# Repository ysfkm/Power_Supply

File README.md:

# Power Supply

## Summary
- Custom linear-regulator power supply boards providing multiple regulated rails from a raw input voltage.
- **v0.1:** 24V input board with four fixed regulators (15V, 12V, 5V, 3V3) plus two variable outputs via jumpers and a buck converter; four-layer 157.5mm x 100mm PCB.
- **v1.1:** Revised ±15V input board delivering +12V and -5V, entirely from linear regulators (12V now derived from 15V instead of 24V, plus a new -5V rail); same 4-layer 157.5mm x 100mm PCB footprint.

## v0.1

### Specs
- **Input:** +24V
- **Output:** +15V, +12V, +5V, +3V3, two variable voltage outputs
- **Description:** one output for each voltage value and two variable outputs via jumpers. Uses four regulators and one buck converter.
- **PCB:** 157.5mm x 100mm / 4 Layer

### 15V Voltage Regulator
- **Input:** 24V, GNDA
- **Output:** 15V, GNDA
- **Maximum Output Current:** 1A
- **Thermal Resistance:** 44.8°C/W

### 12V Voltage Regulator
- **Input:** 24V, GNDA
- **Output:** 12V, GNDA
- **Maximum Output Current:** 1A
- **Thermal Resistance:** 44.8°C/W

### 5V Voltage Regulator
- **Input:** 24V, GNDA
- **Output:** 5V, GNDA
- **Maximum Output Current:** 1.2A
- **9V Buck Converter Thermal Resistance:** 50°C/W
- **5V Linear Regulator Thermal Resistance:** 44.8°C/W

### 3V3 Voltage Regulator
- **Input:** 9V, GNDA
- **Output:** 3V3, GNDA
- **Maximum Output Current:** 5A
- **Thermal Resistance:** 44.8°C/W

### Design Process
- Thermal vias for each regulator for heat dissipation
- Buck converter routed to minimize loop area of interference
- Built four voltage regulators separately, then tested out ideas on how to put together a combined power supply board
- Settled on two variable outputs and four constant outputs

## v1.1

### Specs
- **Input:** +15V, -15V, GNDA
- **Output:** +12V, -5V, GNDA
- **Description:** three output ports for each voltage value. All regulated from linear regulators
- **PCB:** 157.5mm x 100mm / 4 Layer

### 12V Voltage Regulator
- **Input:** 15V, GNDA
- **Output:** 12V, GNDA
- **Maximum Output Current:** 1.5A
- **Thermal Resistance:** 19°C/W

### -5V Voltage Regulator
- **Input:** -15V, GNDA
- **Output:** -5V, GNDA
- **Maximum Output Current:** 1A
- **Thermal Resistance:** 65°C/W

### Design Changes
- Needed -5V supply so made a new version of the board with 12V and -5V
- 12V now regulated from 15V instead of 24V, so used a different regulator

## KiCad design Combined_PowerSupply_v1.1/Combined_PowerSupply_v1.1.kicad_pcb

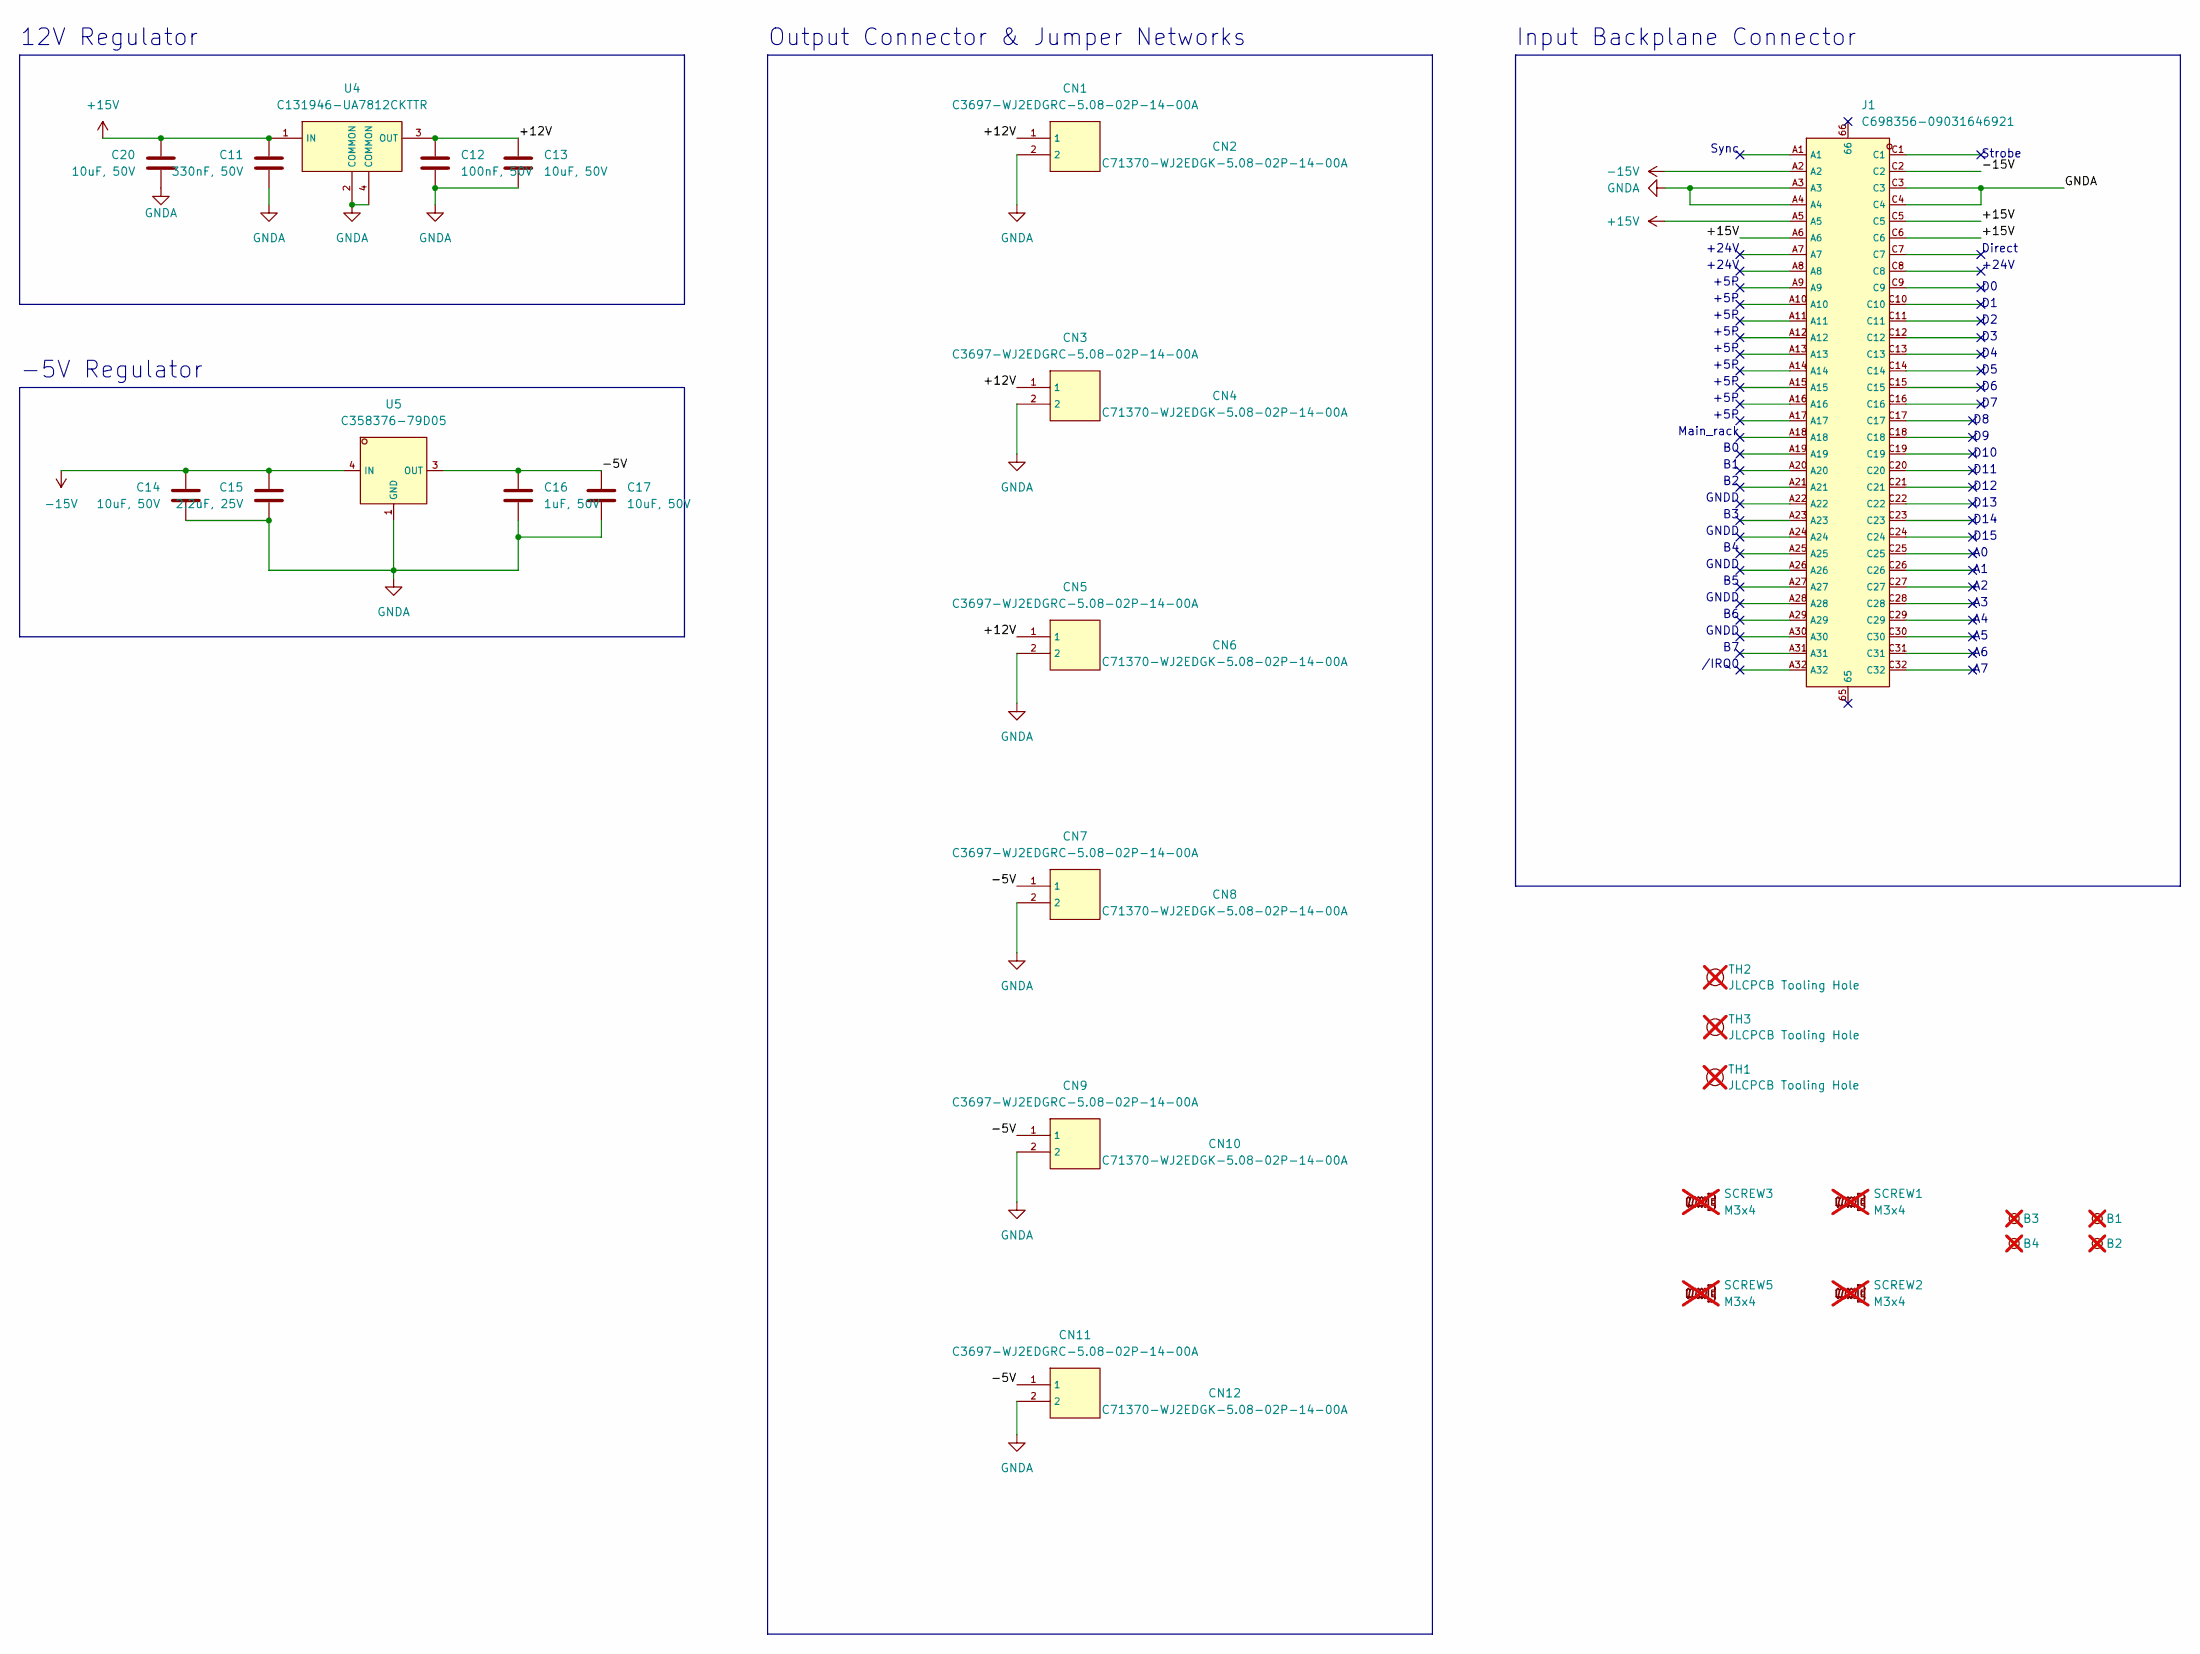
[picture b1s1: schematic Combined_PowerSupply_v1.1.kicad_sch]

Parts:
B1, B2, B3, B4: M3 Mounting Hole; MountingHole_3.2mm_M3_DIN965_Pad; not fitted
C11: 330nF, 50V; C_0603_1608Metric; LCSC C282682
C12: 100nF, 50V; C_0603_1608Metric; LCSC C14663
C13, C14, C17, C20: 10uF, 50V; C_1206_3216Metric; LCSC C13585
C15: 2.2uF, 25V; C_0603_1608Metric; LCSC C57895
C16: 1uF, 50V; C_0603_1608Metric; LCSC C15849
CN1, CN3, CN5, CN7, CN9, CN11: C3697-WJ2EDGRC-5.08-02P-14-00A; C3697-CONN-TH_2P-P5.08_WJ2EDGRC-5.08-2P; LCSC C3697
CN2, CN4, CN6, CN8, CN10, CN12: C71370-WJ2EDGK-5.08-02P-14-00A; C71370-FL_001; LCSC C71370
J1: C698356-09031646921; C698356-CONN-TH_64P-P2.54_HARTING_09031646921; LCSC C698356
SCREW1, SCREW2, SCREW3, SCREW5: M3x4; SCREW_M3; not fitted
TH1, TH2, TH3: JLCPCB Tooling Hole; ToolingHoles; not fitted
U4: C131946-UA7812CKTTR; C131946-TO-263-3L_L10.0-W9.2-P2.54-TL; LCSC C131946
U5: C358376-79D05; C358376-TO-252-2_L6.5-W6.1-P4.58-LS10.0-BR; LCSC C358376

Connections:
+15V: C11.1, C20.1, J1.A5, J1.A6, J1.C5, J1.C6, U4.1 (IN)
-15V: C14.1, C15.1, J1.A2, J1.C2, U5.4 (IN)
/+12V: C12.1, C13.1, CN1.1, CN3.1, CN5.1, U4.3 (OUT)
/-5V: C16.1, C17.1, CN7.1, CN9.1, CN11.1, U5.3 (OUT)
GNDA: C11.2, C12.2, C13.2, C14.2, C15.2, C16.2, C17.2, C20.2, CN1.2, CN3.2, CN5.2, CN7.2, CN9.2, CN11.2, J1.A3, J1.A4, J1.C3, J1.C4, U4.2 (COMMON), U4.4 (COMMON), U5.1 (GND)

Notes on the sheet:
+24V
+5P
Main_rack
D15
Strobe
GNDD
D13
-5V Regulator
D14
/IRQ0
Input Backplane Connector
Direct
Sync
D10
12V Regulator
Output Connector & Jumper Networks
D12
D11

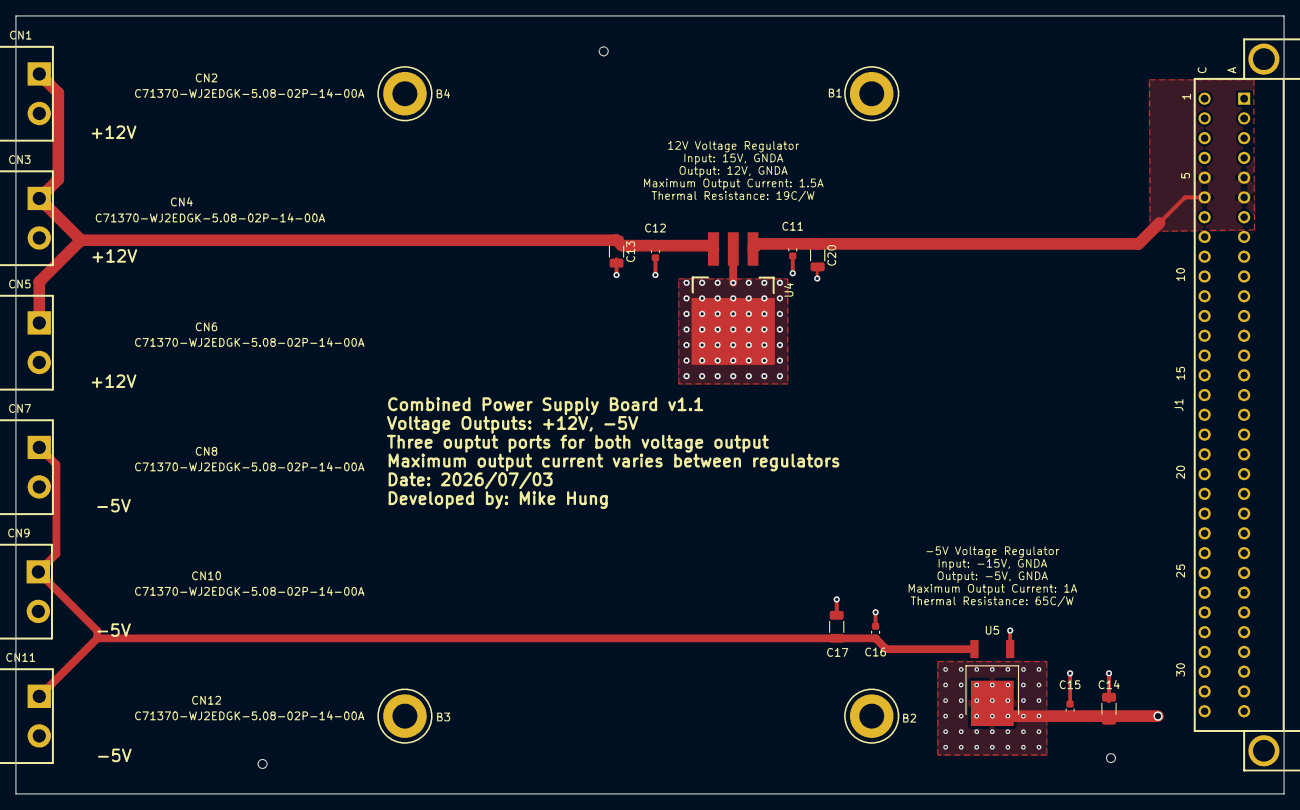
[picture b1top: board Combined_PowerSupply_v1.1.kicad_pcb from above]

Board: 4 copper layers, 163.0 x 100.0 mm, 34 parts (0 on the bottom side), 5 nets.

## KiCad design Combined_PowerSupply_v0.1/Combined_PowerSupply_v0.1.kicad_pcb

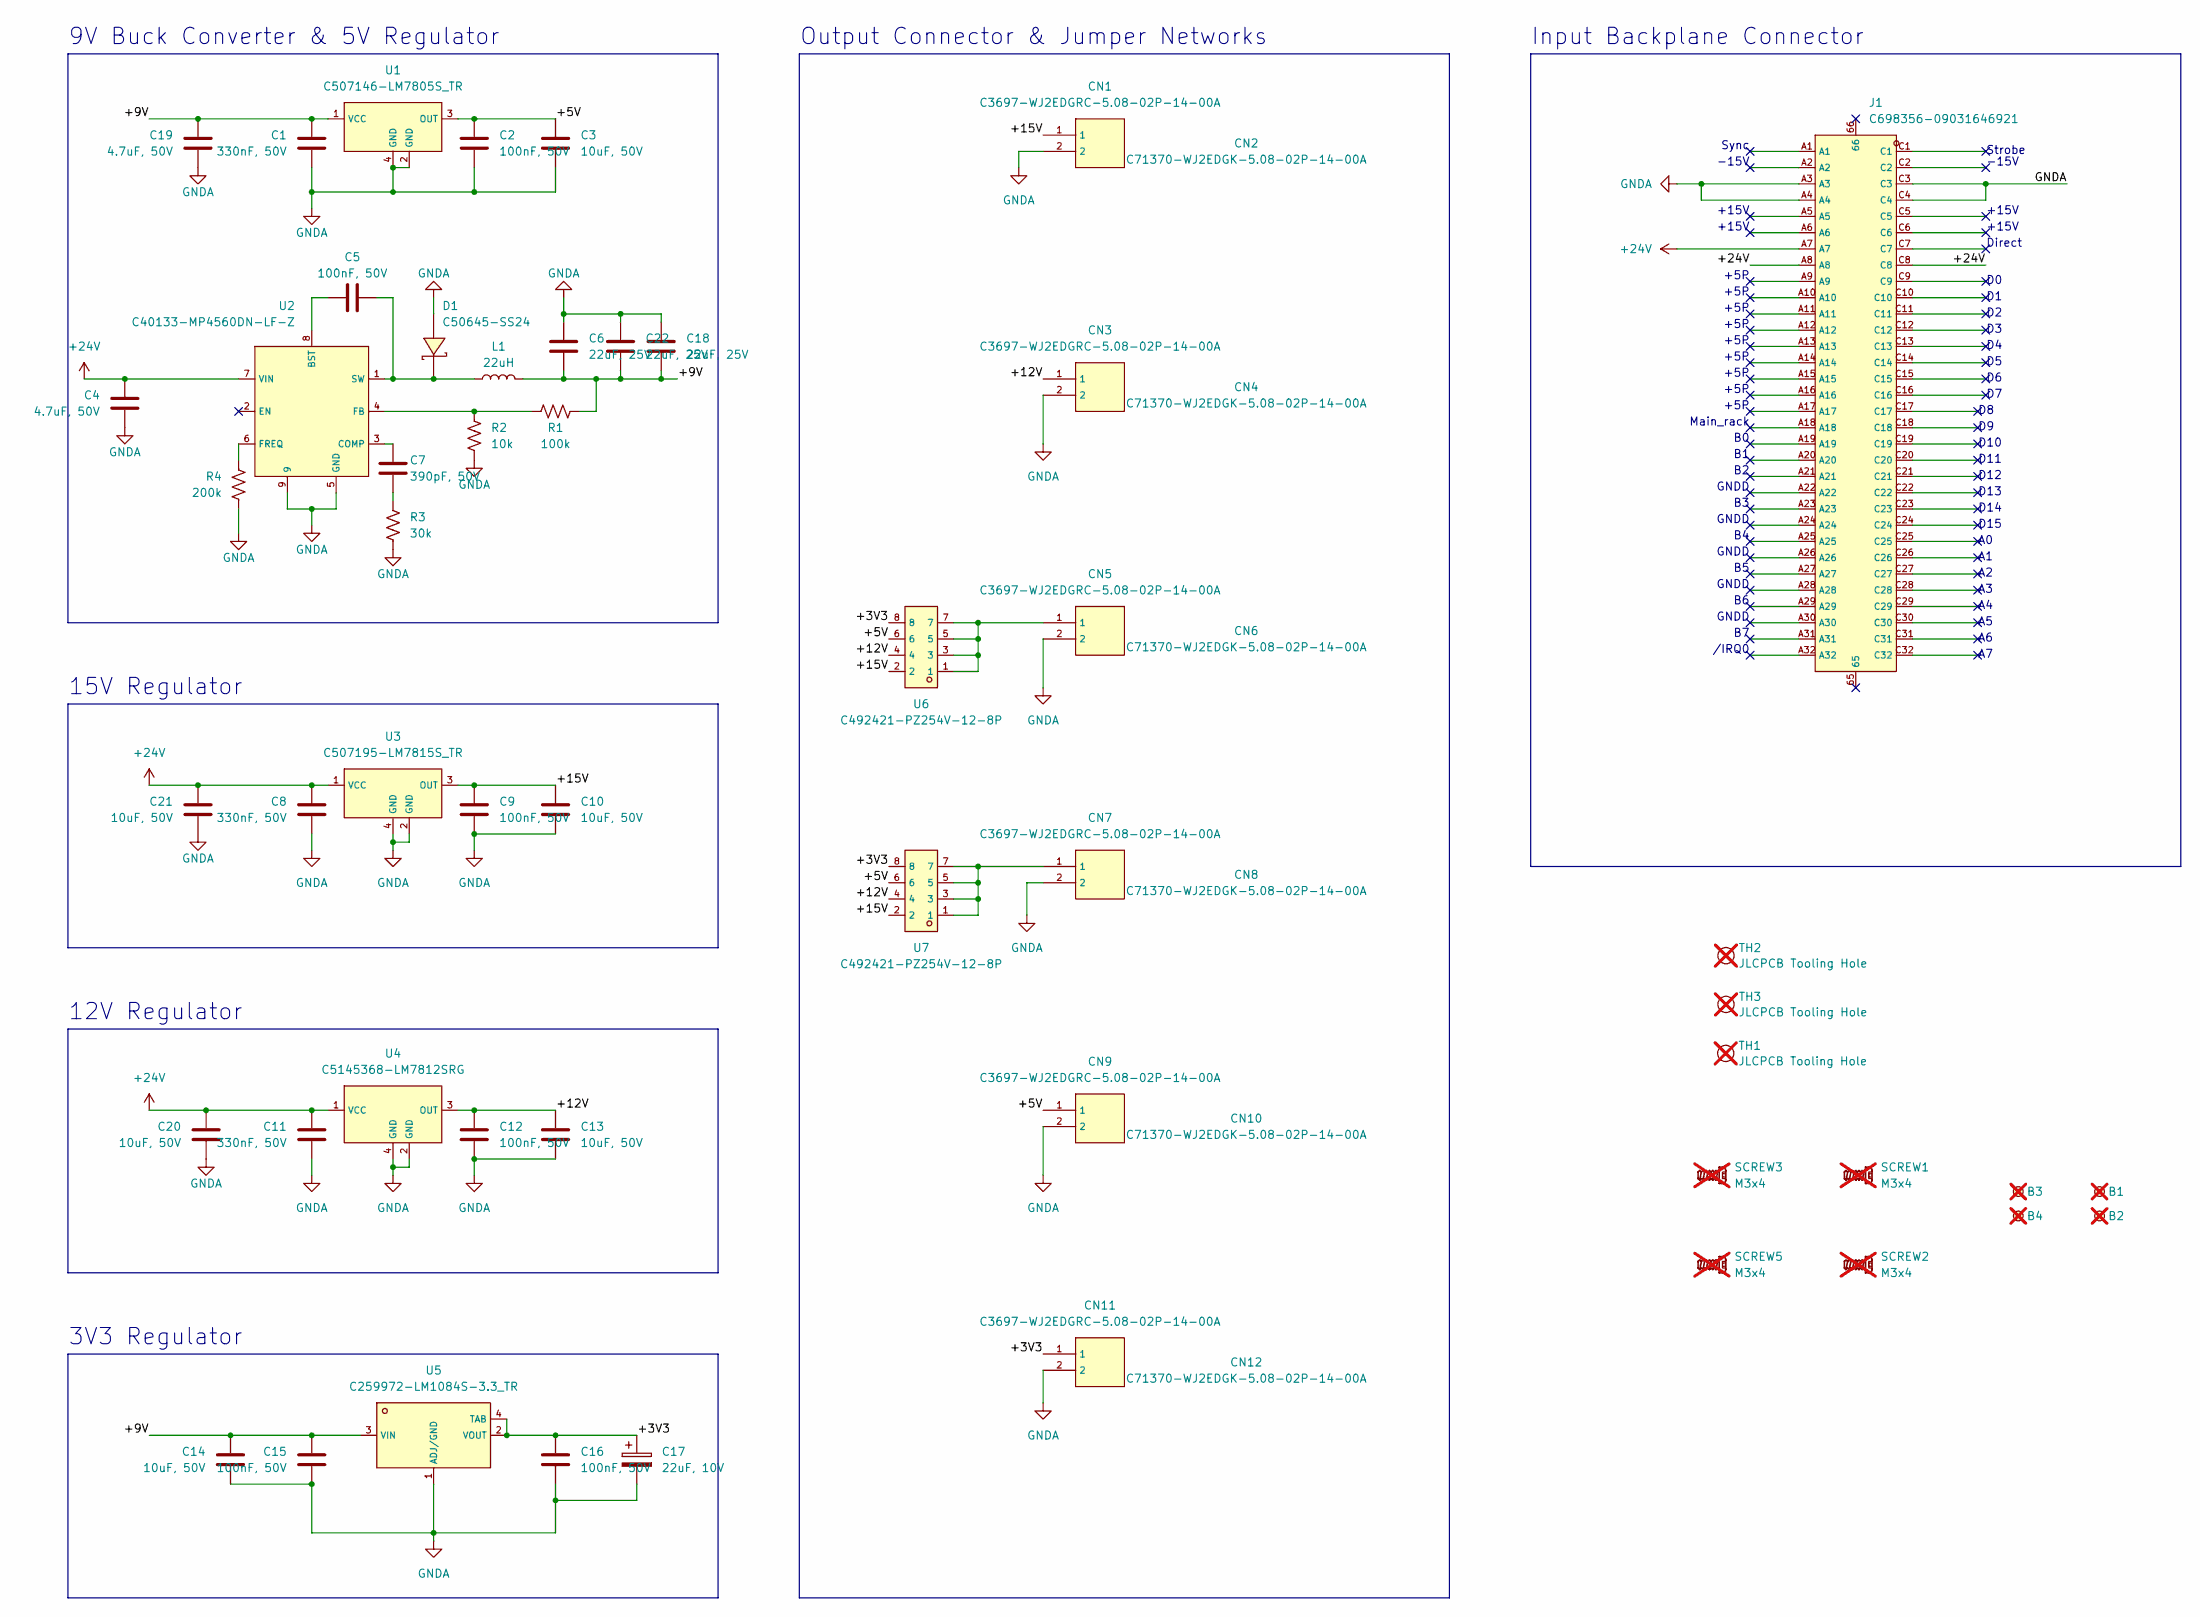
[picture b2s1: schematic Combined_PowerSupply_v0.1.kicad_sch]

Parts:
B1, B2, B3, B4: M3 Mounting Hole; MountingHole_3.2mm_M3_DIN965_Pad; not fitted
C1, C8, C11: 330nF, 50V; C_0603_1608Metric; LCSC C282682
C2, C5, C9, C12, C15, C16: 100nF, 50V; C_0603_1608Metric; LCSC C14663
C3, C10, C13, C14, C20, C21: 10uF, 50V; C_1206_3216Metric; LCSC C13585
C4, C19: 4.7uF, 50V; C_0805_2012Metric; LCSC C437557
C6, C18, C22: 22uF, 25V; C_1206_3216Metric; LCSC C12891
C7: 390pF, 50V; C_0402_1005Metric; LCSC C76967
C17: 22uF, 10V; C11366-CASE-A_3216; LCSC C11366
CN1, CN3, CN5, CN7, CN9, CN11: C3697-WJ2EDGRC-5.08-02P-14-00A; C3697-CONN-TH_2P-P5.08_WJ2EDGRC-5.08-2P; LCSC C3697
CN2, CN4, CN6, CN8, CN10, CN12: C71370-WJ2EDGK-5.08-02P-14-00A; C71370-FL_001; LCSC C71370
D1: C50645-SS24; C50645-SMA_L4.3-W2.6-LS5.2-RD; LCSC C50645
J1: C698356-09031646921; C698356-CONN-TH_64P-P2.54_HARTING_09031646921; LCSC C698356
L1: 22uH; C475917-IND-SMD_L10.0-W10.0-LS11.0; LCSC C475917
R1: 100k; R_0402_1005Metric; LCSC C25741
R2: 10k; R_0402_1005Metric; LCSC C25744
R3: 30k; R_0603_1608Metric; LCSC C22984
R4: 200k; R_0402_1005Metric; LCSC C25764
SCREW1, SCREW2, SCREW3, SCREW5: M3x4; SCREW_M3; not fitted
TH1, TH2, TH3: JLCPCB Tooling Hole; ToolingHoles; not fitted
U1: C507146-LM7805S_TR; C507146-TO-263-3_L8.6-W10.2-P2.54-LS14.4-BR; LCSC C507146
U2: C40133-MP4560DN-LF-Z; C40133-SOIC-8_L4.9-W3.9-P1.27-LS6.0-BL-EP3.1-1; LCSC C40133
U3: C507195-LM7815S_TR; C507195-TO-263-3_L8.6-W10.2-P2.54-LS14.4-BR; LCSC C507195
U4: C5145368-LM7812SRG; C5145368-TO-263-3_L8.6-W10.2-P2.54-LS14.4-BR; LCSC C5145368
U5: C259972-LM1084S-3.3_TR; C259972-TO-263-3_L8.6-W10.2-P2.54-LS14.4-TL; LCSC C259972
U6, U7: C492421-PZ254V-12-8P; C492421-HDR-TH_8P-P2.54-V-M-R2-C4-S2.54; LCSC C492421

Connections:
+24V: C4.1, C8.1, C11.1, C20.1, C21.1, J1.A7, J1.A8, J1.C8, U2.7 (VIN), U3.1 (VCC), U4.1 (VCC)
/+3V3: C16.1, C17.1, CN11.1, U5.2 (VOUT), U5.4 (TAB), U6.8, U7.8
/+5V: C2.1, C3.1, CN9.1, U1.3 (OUT), U6.6, U7.6
/+9V: C1.1, C6.2, C14.1, C15.1, C18.2, C19.1, C22.2, L1.2, R1.2, U1.1 (VCC), U5.3 (VIN)
/+12V: C12.1, C13.1, CN3.1, U4.3 (OUT), U6.4, U7.4
/+15V: C9.1, C10.1, CN1.1, U3.3 (OUT), U6.2, U7.2
GNDA: C1.2, C2.2, C3.2, C4.2, C6.1, C8.2, C9.2, C10.2, C11.2, C12.2, C13.2, C14.2, C15.2, C16.2, C17.2, C18.1, C19.2, C20.2, C21.2, C22.1, CN1.2, CN3.2, CN5.2, CN7.2, CN9.2, CN11.2, D1.2 (A), J1.A3, J1.A4, J1.C3, J1.C4, R2.2, R3.2, R4.2, U1.2 (GND), U1.4 (GND), U2.5 (GND), U2.9, U3.2 (GND), U3.4 (GND), U4.2 (GND), U4.4 (GND), U5.1 (ADJ/GND)
unnamed: C7.1, R3.1
unnamed: CN5.1, U6.1, U6.3, U6.5, U6.7
unnamed: CN7.1, U7.1, U7.3, U7.5, U7.7
unnamed: C5.2, D1.1 (K), L1.1, U2.1 (SW)
unnamed: C5.1, U2.8 (BST)
unnamed: C7.2, U2.3 (COMP)
unnamed: R1.1, R2.1, U2.4 (FB)
unnamed: R4.1, U2.6 (FREQ)

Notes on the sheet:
+5P
Main_rack
D15
Strobe
GNDD
D13
15V Regulator
+15V
3V3 Regulator
D14
/IRQ0
-15V
Input Backplane Connector
Direct
Sync
D10
12V Regulator
9V Buck Converter & 5V Regulator
Output Connector & Jumper Networks
D12
D11

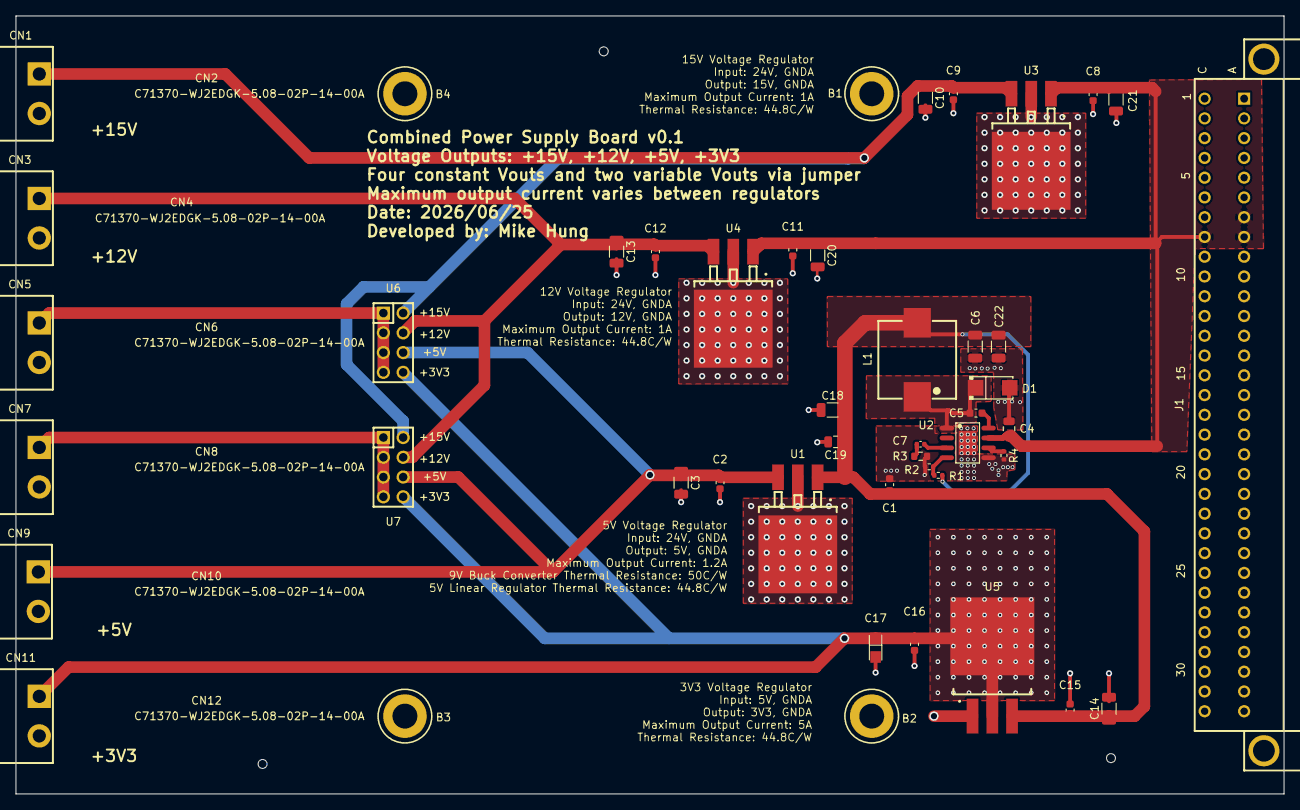
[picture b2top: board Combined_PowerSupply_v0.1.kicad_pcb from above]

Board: 4 copper layers, 163.0 x 100.0 mm, 59 parts (0 on the bottom side), 15 nets.

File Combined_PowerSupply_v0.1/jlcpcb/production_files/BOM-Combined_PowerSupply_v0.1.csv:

Comment,Designator,Footprint,LCSC,Quantity
"22uF, 10V",C17,C11366-CASE-A_3216,C11366,1
"22uF, 25V","C18,C22,C6",C_1206_3216Metric,C12891,3
"10uF, 50V","C10,C13,C14,C20,C21,C3",C_1206_3216Metric,C13585,6
"100nF, 50V","C12,C15,C16,C2,C5,C9",C_0603_1608Metric,C14663,6
30k,R3,R_0603_1608Metric,C22984,1
100k,R1,R_0402_1005Metric,C25741,1
10k,R2,R_0402_1005Metric,C25744,1
200k,R4,R_0402_1005Metric,C25764,1
C259972-LM1084S-3.3_TR,U5,C259972-TO-263-3_L8.6-W10.2-P2.54-LS14.4-TL,C259972,1
"330nF, 50V","C1,C11,C8",C_0603_1608Metric,C282682,3
C3697-WJ2EDGRC-5.08-02P-14-00A,"CN1,CN11,CN3,CN5,CN7,CN9",C3697-CONN-TH_2P-P5.08_WJ2EDGRC-5.08-2P,C3697,6
C40133-MP4560DN-LF-Z,U2,C40133-SOIC-8_L4.9-W3.9-P1.27-LS6.0-BL-EP3.1-1,C40133,1
"4.7uF, 50V","C19,C4",C_0805_2012Metric,C437557,2
22uH,L1,C475917-IND-SMD_L10.0-W10.0-LS11.0,C475917,1
C492421-PZ254V-12-8P,"U6,U7",C492421-HDR-TH_8P-P2.54-V-M-R2-C4-S2.54,C492421,2
C50645-SS24,D1,C50645-SMA_L4.3-W2.6-LS5.2-RD,C50645,1
C507146-LM7805S_TR,U1,C507146-TO-263-3_L8.6-W10.2-P2.54-LS14.4-BR,C507146,1
C507195-LM7815S_TR,U3,C507195-TO-263-3_L8.6-W10.2-P2.54-LS14.4-BR,C507195,1
C5145368-LM7812SRG,U4,C5145368-TO-263-3_L8.6-W10.2-P2.54-LS14.4-BR,C5145368,1
C5173368-9001-14641C00A,J1,C5173368-CONN-TH_WINGTAT_9001-14641C00A,C5173368,1
C71370-WJ2EDGK-5.08-02P-14-00A,"CN10,CN12,CN2,CN4,CN6,CN8",C71370-FL_001,C71370,6
"390pF, 50V",C7,C_0402_1005Metric,C76967,1
